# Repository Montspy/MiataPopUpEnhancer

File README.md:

# MiataPopUpEnhancer
Plug and play module to add wink to NA Miata pop up headlights

Features targeted:
- [ ] Plug'n'play in harness (no cutting, soldering nonsense)
- [ ] Indepedent control of left and right headlight motor
- [ ] Execute movements sequences via short or long presses combo of the pop up button
- [ ] Maintain OEM function of the pop up button and the headlight switch
- [ ] Drag'n'drop programming (via USB Mass storage)
- [ ] TBD: Sleepy eyes
- [ ] TBD: Control and settings via app (BLE)

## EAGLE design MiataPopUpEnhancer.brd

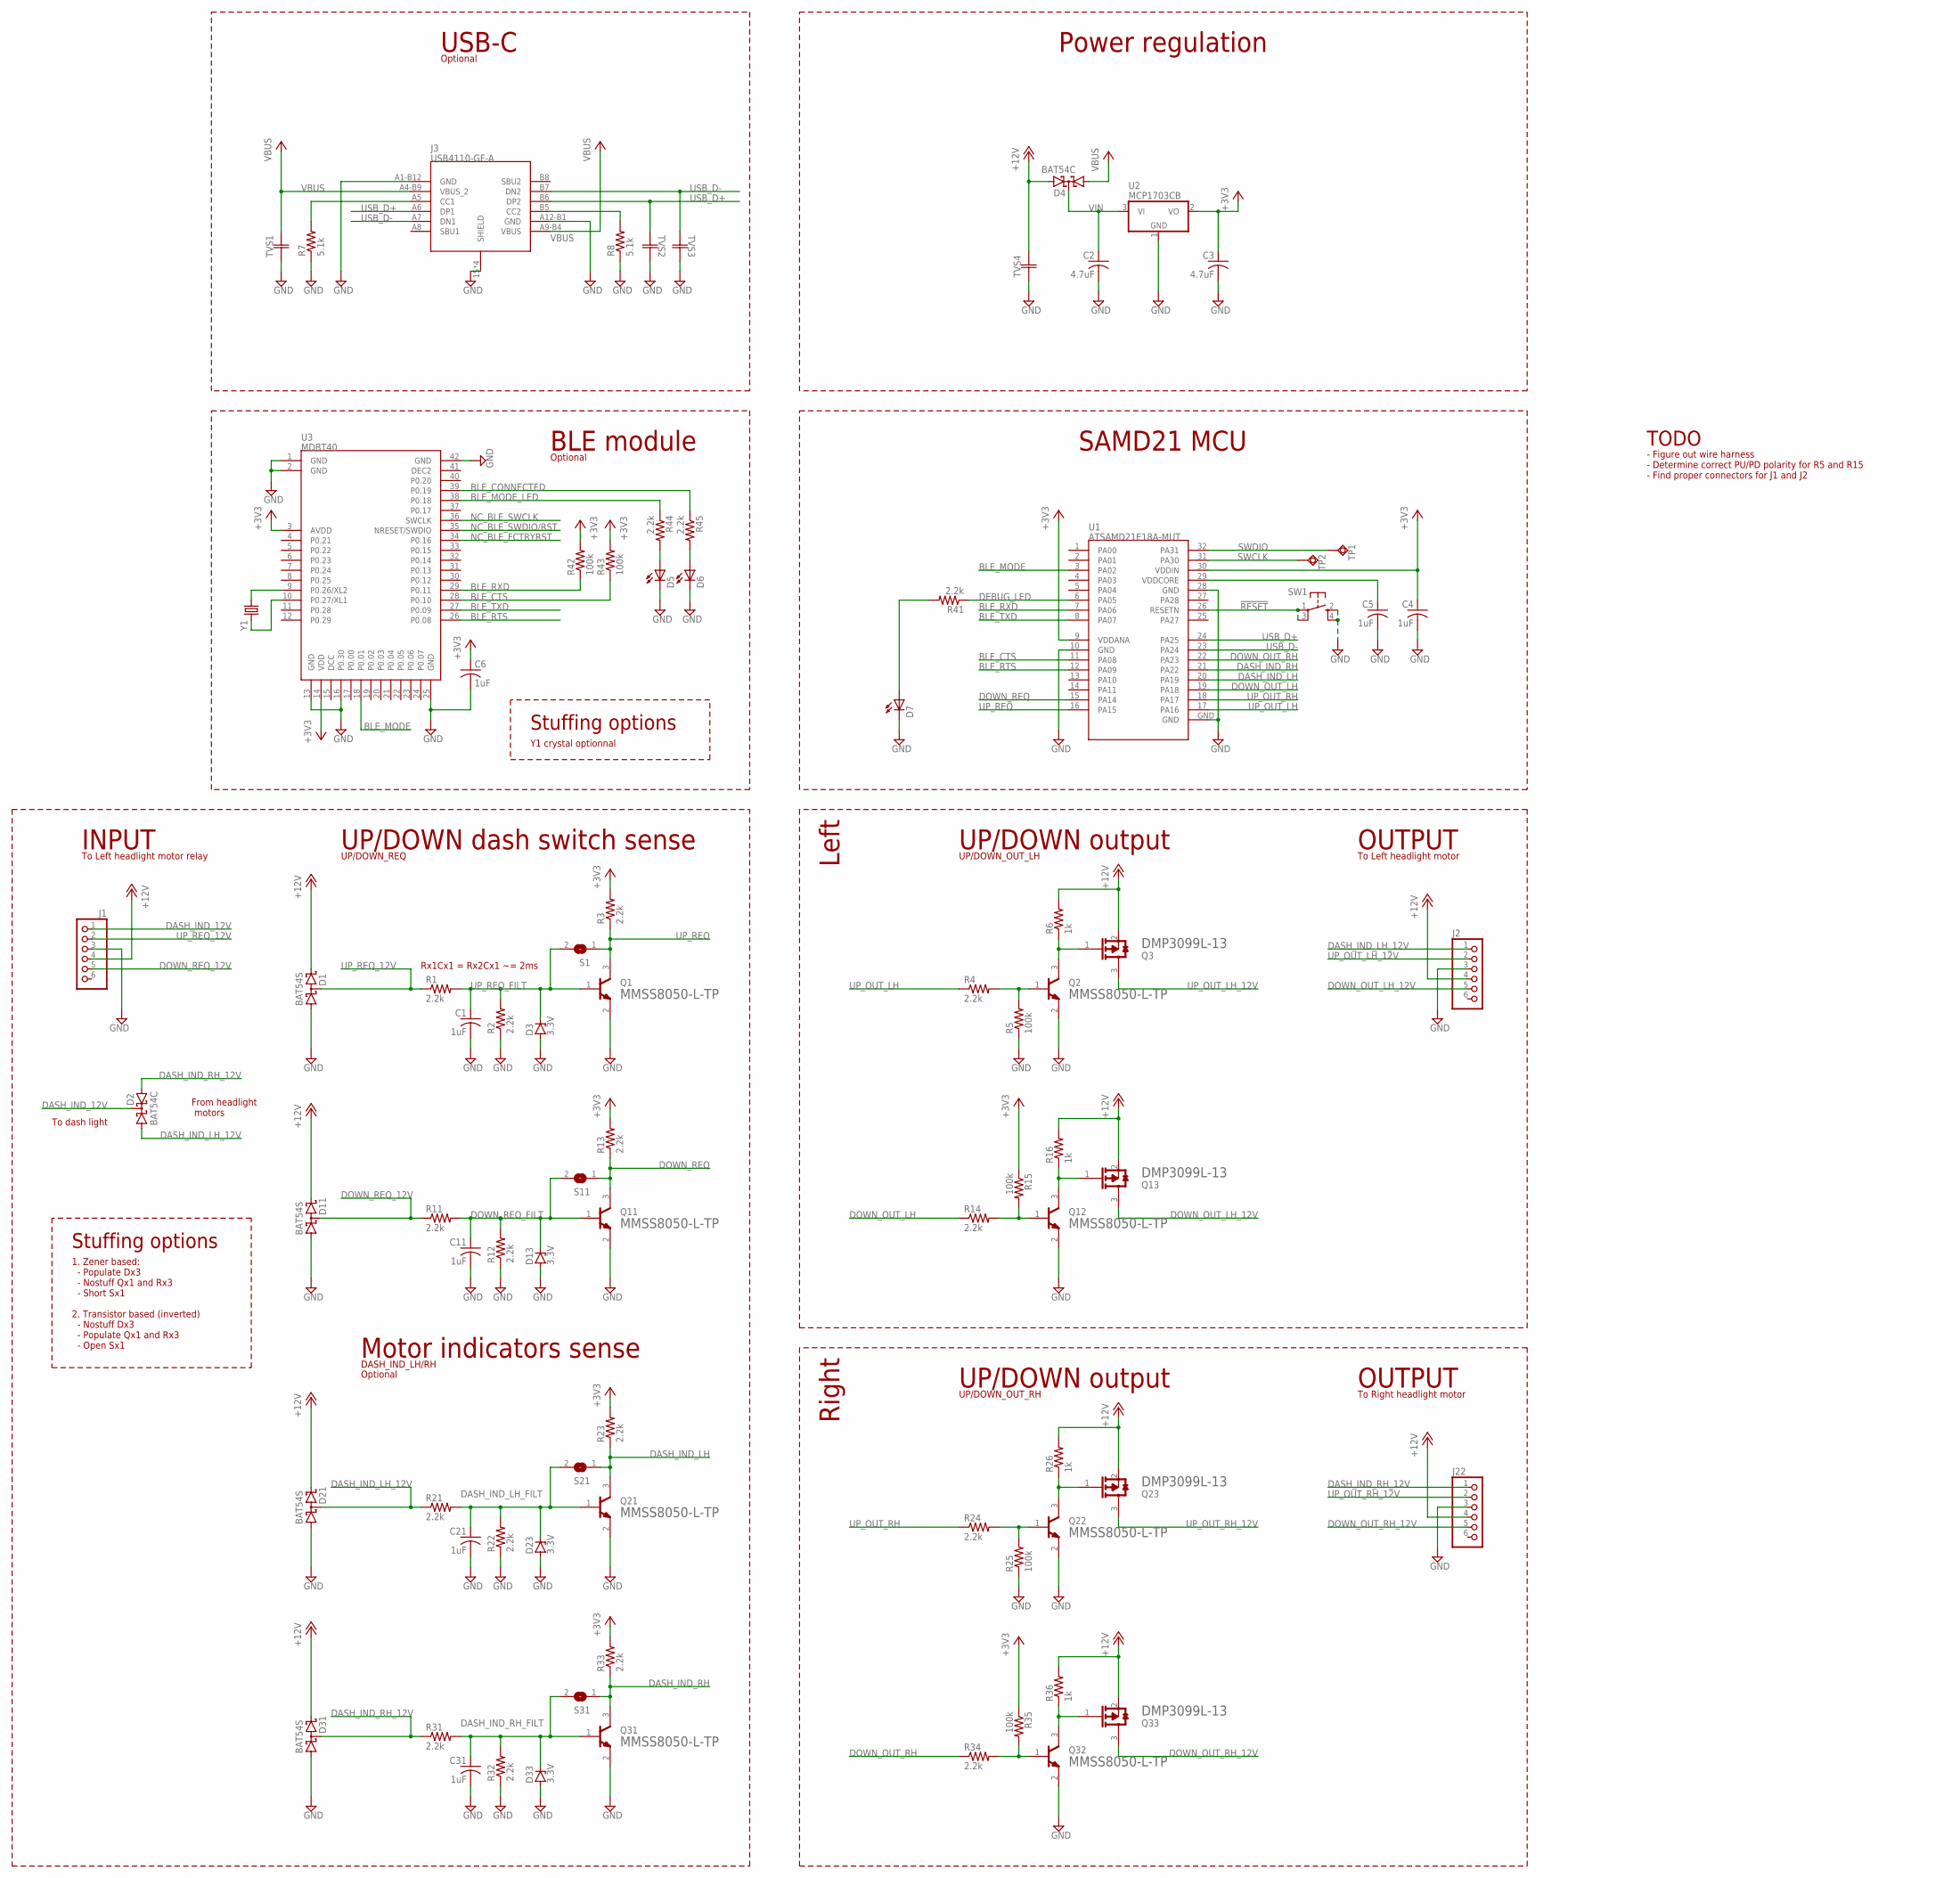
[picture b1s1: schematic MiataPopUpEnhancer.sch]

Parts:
C1, C4, C5, C6, C11, C21, C31: 1uF; C0603
C2: 4.7uF; C0603K
C3: 4.7uF; C0603
D1, D11, D21, D31: BAT54S; SOT23
D2, D4: BAT54C; SOT23
D3, D13, D23, D33: 3.3V; TO236
D5, D6, D7: LEDCHIPLED_0603; CHIPLED_0603
J1, J2, J22: PINHD-1X6LOCK; 1X06-BIGLOCK
J3: USB4110-GF-A; USB4110-GF-A_GCT
Q1, Q2, Q11, Q12, Q21, Q22, Q31, Q32: MICRO_COMMERCIAL_MMSS8050-L-TPMICRO_COMMERCIAL_MM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; MICRO_COMMERCIAL_MMSS8050-L-TP_0
Q3, Q13, Q23, Q33: DIODES_INC_DMP3099L-13DIODES_INC_DMP3099L-13_0_0; DIODES_INC_DMP3099L-13_0
R1, R2, R3, R4, R11, R12, R13, R14, R21, R22, R23, R24, R31, R32, R33, R34, R41, R44, R45: 2.2k; R0603
R5, R15, R25, R35, R42, R43: 100k; R0603
R6, R16, R26, R36: 1k; R0603
R7, R8: 5.1k; R0603
S1, S11, S21, S31: SJ
SW1: KMR2
TP1, TP2: TPSQB2,54; B2,54
TVS1, TVS2, TVS3, TVS4: ESDU02A5V5R17V; CAP_ESDU02_STP
U1: ATSAMD21E18A-MUT; QFN32
U2: MCP1703CB; SOT23
U3: MDBT40
Y1: ABS25-32.768KHZ-T; MM20SS

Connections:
!RESET: SW1.1, SW1.3 (P1), U1.26 (RESETN)
+3V3: C3.1, C4.1, C6.1, R3.2, R13.2, R15.1, R23.2, R33.2, R35.1, R42.2, R43.2, U1.9 (VDDANA), U1.30 (VDDIN), U2.2 (VO), U3.3 (AVDD), U3.14 (VDD)
+12V: D1.2 (C2), D4.2 (A2), D11.2 (C2), D21.2 (C2), D31.2 (C2), J1.4, J2.4, J22.4, Q3.2 (S), Q13.2 (S), Q23.2 (S), Q33.2 (S), R6.2, R16.2, R26.2, R36.2, TVS4.1
BLE_CONNECTED: R45.1, U3.39 (P0.19)
BLE_CTS: R43.1, U1.11 (PA08), U3.28 (P0.10)
BLE_MODE: U1.3 (PA02), U3.18 (P0.01)
BLE_MODE_LED: R44.1, U3.38 (P0.18)
BLE_RTS: U1.12 (PA09), U3.26 (P0.08)
BLE_RXD: R42.1, U1.7 (PA06), U3.29 (P0.11)
BLE_TXD: U1.8 (PA07), U3.27 (P0.09)
CC1: J3.A5 (CC1), R7.2
CC2: J3.B5 (CC2), R8.2
DASH_IND_12V: D2.3 (CC), J1.1
DASH_IND_LH: Q21.3 (C), R23.1, S21.1, U1.20 (PA19)
DASH_IND_LH_12V: D2.1 (A1), D21.3 (C1A2), J2.1, R21.1
DASH_IND_LH_FILT: C21.1, D23.C, Q21.1 (B), R21.2, R22.2, S21.2
DASH_IND_RH: Q31.3 (C), R33.1, S31.1, U1.21 (PA22)
DASH_IND_RH_12V: D2.2 (A2), D31.3 (C1A2), J22.1, R31.1
DASH_IND_RH_FILT: C31.1, D33.C, Q31.1 (B), R31.2, R32.2, S31.2
DEBUG_LED: R41.1, U1.6 (PA05)
DOWN_OUT_LH: R14.1, U1.19 (PA18)
DOWN_OUT_LH_12V: J2.5, Q13.3 (D)
DOWN_OUT_RH: R34.1, U1.22 (PA23)
DOWN_OUT_RH_12V: J22.5, Q33.3 (D)
DOWN_REQ: Q11.3 (C), R13.1, S11.1, U1.15 (PA14)
DOWN_REQ_12V: D11.3 (C1A2), J1.5, R11.1
DOWN_REQ_FILT: C11.1, D13.C, Q11.1 (B), R11.2, R12.2, S11.2
GND: C1.2, C2.2, C3.2, C4.2, C5.2, C6.2, C11.2, C21.2, C31.2, D1.1 (A1), D3.A, D5.C, D6.C, D7.C, D11.1 (A1), D13.A, D21.1 (A1), D23.A, D31.1 (A1), D33.A, J1.3, J2.3, J3.15 (SHIELD), J3.16 (SHIELD), J3.17 (SHIELD), J3.18 (SHIELD), J3.A1-B12 (GND), J3.A12-B1 (GND), J22.3, Q1.2 (E), Q2.2 (E), Q11.2 (E), Q12.2 (E), Q21.2 (E), Q22.2 (E), Q31.2 (E), Q32.2 (E), R2.1, R5.1, R7.1, R8.1, R12.1, R22.1, R25.1, R32.1, SW1.2 (S), SW1.4 (S1), TVS1.1, TVS2.1, TVS3.1, TVS4.2, U1.10 (GND), U1.28 (GND), U1.GND, U2.1 (GND), U3.1 (GND), U3.2 (GND), U3.13 (GND), U3.16 (P0.30), U3.25 (GND), U3.42 (GND)
unnamed: Q12.3 (C), Q13.1 (G), R16.1
unnamed: Q2.3 (C), Q3.1 (G), R6.1
unnamed: Q12.1 (B), R14.2, R15.2
unnamed: Q2.1 (B), R4.2, R5.2
unnamed: Q22.3 (C), Q23.1 (G), R26.1
unnamed: Q22.1 (B), R24.2, R25.2
unnamed: Q32.3 (C), Q33.1 (G), R36.1
unnamed: Q32.1 (B), R34.2, R35.2
unnamed: D5.A, R44.2
unnamed: D6.A, R45.2
unnamed: D7.A, R41.2
NC_BLE_FCTRYRST: U3.34 (P0.16)
NC_BLE_SWCLK: U3.36 (SWCLK)
NC_BLE_SWDIO/RST: U3.35 (NRESET/SWDIO)
SWCLK: TP2.TP, U1.31 (PA30)
SWDIO: TP1.TP, U1.32 (PA31)
UP_OUT_LH: R4.1, U1.17 (PA16)
UP_OUT_LH_12V: J2.2, Q3.3 (D)
UP_OUT_RH: R24.1, U1.18 (PA17)
UP_OUT_RH_12V: J22.2, Q23.3 (D)
UP_REQ: Q1.3 (C), R3.1, S1.1, U1.16 (PA15)
UP_REQ_12V: D1.3 (C1A2), J1.2, R1.1
UP_REQ_FILT: C1.1, D3.C, Q1.1 (B), R1.2, R2.2, S1.2
USB_D+: J3.A6 (DP1), J3.B6 (DP2), TVS2.2, U1.24 (PA25)
USB_D-: J3.A7 (DN1), J3.B7 (DN2), TVS3.2, U1.23 (PA24)
VBUS: D4.1 (A1), J3.A4-B9 (VBUS_2), J3.A9-B4 (VBUS), TVS1.2
VDDCORE: C5.1, U1.29 (VDDCORE)
VIN: C2.1, D4.3 (CC), U2.3 (VI)
XL1: U3.10 (P0.27/XL1), Y1.4 (2)
XL2: U3.9 (P0.26/XL2), Y1.1

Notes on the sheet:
INPUT
OUTPUT
UP/DOWN dash switch sense
UP/DOWN output
Rx1Cx1 = Rx2Cx1 ~= 2ms
BLE module
SAMD21 MCU
To Left headlight motor relay
To Left headlight motor
Optional
TODO
- Figure out wire harness - Determine correct PU/PD polarity for R5 and R15 - Find proper connectors for J1 and J2
Stuffing options
1. Zener based: - Populate Dx3 - Nostuff Qx1 and Rx3 - Short Sx1 2. Transistor based (inverted) - Nostuff Dx3 - Populate Qx1 and Rx3 - Open Sx1
Left
To Right headlight motor
Right
From headlight motors
To dash light
Power regulation
USB-C
Motor indicators sense
UP/DOWN_REQ
DASH_IND_LH/RH
UP/DOWN_OUT_LH
UP/DOWN_OUT_RH
Y1 crystal optionnal

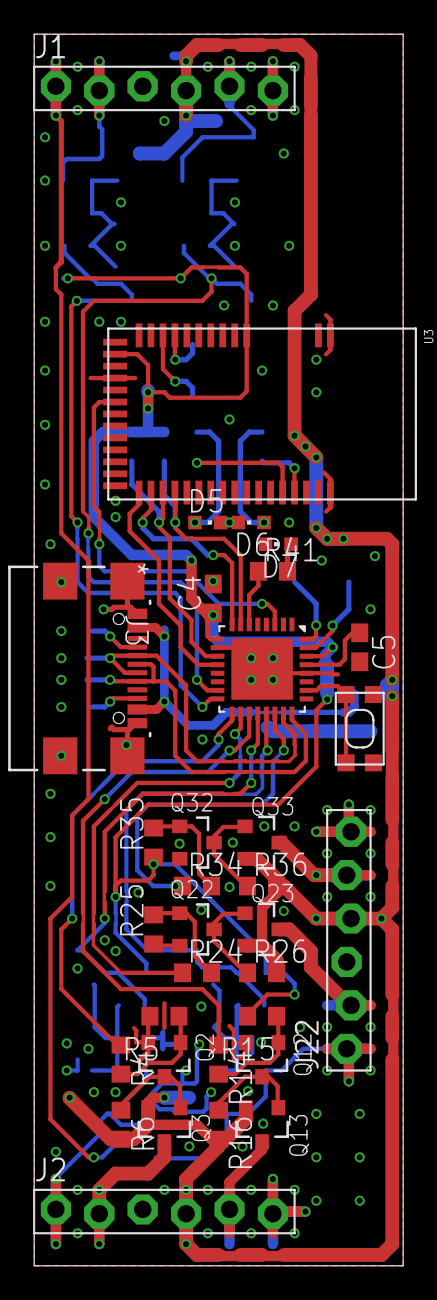
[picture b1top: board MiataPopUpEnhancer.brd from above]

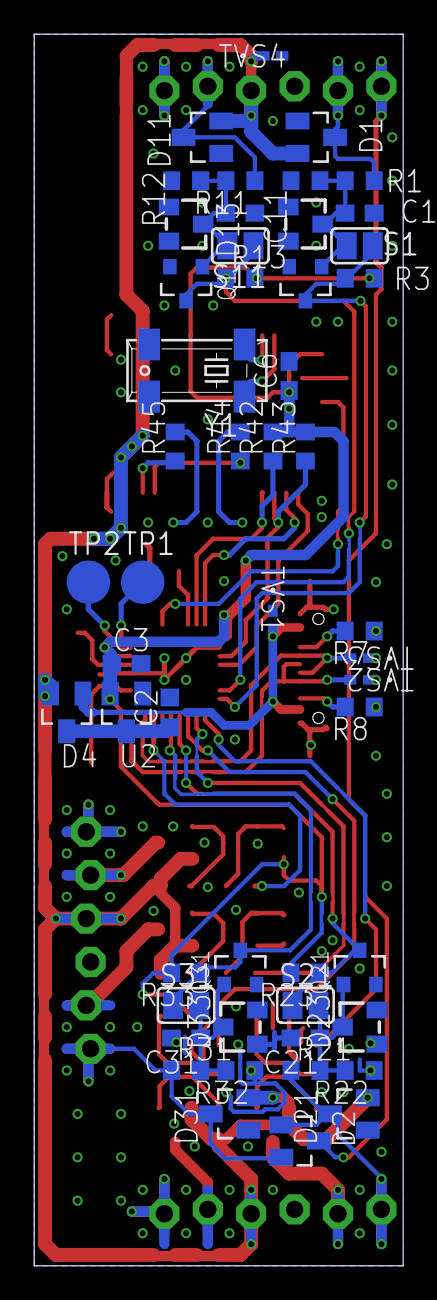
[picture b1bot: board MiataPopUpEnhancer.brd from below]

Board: 2 copper layers, 21.6 x 72.1 mm, 84 parts (51 on the bottom side), 55 nets.

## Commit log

2021-11-07 First darft of schematic
2021-11-07 Useful bookmarks
2021-11-07 Adds connectors documentation
2021-11-08 Adds BLE module Adds Motor indicator sense circuitry Simplifies INPUT circuitry for UP/DOWN requests Adds circuit protections
2021-11-08 Adds PDF version of sch
2021-11-17 Adds first draft of board file. Updates USBC receptable footprint Minor corrections to schematic
2021-11-18 Continues routing and cleanup of south end of board
2021-11-19 First complete layout. Still using headers for connectors

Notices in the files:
parts and their libraries:
COPYRIGHT: Copyright (C) 2021 Ultra Librarian. All rights reserved.
